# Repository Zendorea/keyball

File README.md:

# Keyball61 Wireless (PMW3610 / nice!nano / ZMK)

A fork of [Yowkees/keyball](https://github.com/Yowkees/keyball) for converting a
**Keyball61** (holykeebs Keyball61 rev2) to a **fully wireless** build:
**nice!nano v2 + ZMK**, with the power-hungry PMW3360 trackball sensor replaced by
the low-power **PMW3610**.

This fork holds the **hardware** side of that conversion — the custom PMW3610
sensor daughterboard. The **firmware** (ZMK) lives in a separate repo.

## What's here

- **[`keyball61_wireless/pmw3610_daughterboard/`](keyball61_wireless/pmw3610_daughterboard/)**
  — the PMW3610 trackball daughterboard: KiCad source, reproducible build
  pipeline, DRC-clean gerbers (ordered from PCBway), BOM, and full design notes.
  A drop-in replacement for the stock Keyball61 ball-reader board that keeps the
  original 7-pin connector and adds a MOTION interrupt line. **See its README.**
- **`keyball61/`** — the upstream Yowkees Keyball61 hardware design data (kept for
  reference: case, PCB, dimensions the daughterboard indexes to).

## Firmware (separate repo)

The wireless ZMK config is **`zmk-config-keyball61-wireless`** (standalone, as ZMK
configs must be). Trackball on `&spi1`: SCK P1.13, SDIO P0.10 (3-wire), CS P0.09,
MOTION P1.11, 2 MHz — based on the proven `tangbonze/zmk-config-Keyball61`.

## Project status

- ✅ Daughterboard: designed, DRC-clean, gerbers ordered (PCBway, ENIG, 1.0 mm)
- ✅ Parts sourced: PMW3610+LM18-LSI (AliExpress), passives/LDO (LCSC), 34 mm ball
- ✅ ZMK config: built (separate repo)
- ⬜ Assemble + flash when hardware arrives
- ⬜ (optional) main-board fork: nice!nano + nice!view

## Credits

Base keyboard design © [Yowkees / Keyball](https://github.com/Yowkees/keyball)
(see `LICENSE`). PMW3610 reference designs: siderakb / badjeff. Kit: holykeebs.

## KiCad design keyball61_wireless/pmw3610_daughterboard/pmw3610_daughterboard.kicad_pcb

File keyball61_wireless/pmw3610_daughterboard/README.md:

# PMW3610 Trackball Daughterboard — Keyball61 Wireless

Drop-in replacement for the stock Keyball61 PMW3360 ball-reader board, redesigned
for the low-power **PMW3610** sensor on a **nice!nano / ZMK** wireless build.
Keeps the stock Keyball **7-pin** connector at the exact original positions (drops
into a stock Keyball main board) and adds a **separate MOTION solder hole** so ZMK
can run the sensor interrupt-driven for best battery life.

**Status: final, DRC-clean, gerbers ordered from PCBway.**

## Board summary
- **23.0 × 25.0 mm**, 2-layer, **1.0 mm**, ENIG. U-shaped outline with a lens slot
  open to the top edge, sized to the **LM18-LSI** lens body.
- **PMW3610 optical center** at the original ball-facing position; connector +
  sensor share the X=11.0 mm centerline (ball centers on the IC via the stock
  Keyball cage).
- **7-pin connector** (CK·IO·G·V·G·CS·RST) at exact stock 2.54 mm positions +
  a separate **MOT** solder hole on the same pitch.
- Full PMW3610 support: **TLV74318** 1.8 V LDO + charge-pump/decoupling caps +
  NRESET & MOTION pull-ups. Solid B.Cu GND pour with stitching vias.
- DRC: **0 unrouted / 0 unconnected / 0 electrical / 0 hole-clearance**
  (5 non-fatal courtyard-overlap advisories — not fab-blocking).

## Files
| File | What it is |
|------|-----------|
| `DESIGN.md` | Full design spec: optics Z-stack, connector, MOTION, datasheet notes. |
| `BOM.csv` | As-built bill of materials with LCSC part numbers + cap-to-pin mapping. |
| `pmw3610_daughterboard.kicad_pcb` / `.kicad_pro` | Final routed board + project. |
| `pmw3610_daughterboard.kicad_dru` | Custom design rules (0.15 mm edge clearance). |
| `pmw3610_kb.pretty/` | The 3 custom footprints used: PMW3610 (siderakb), 7-pin connector, MOTION pad. |
| `fp-lib-table` | Resolves the local footprint lib on open. |
| `gerbers/` + `pmw3610_daughterboard_gerbers.zip` | Fab package (PCBway-ready): 7 gerbers + separate PTH/NPTH Excellon drills. |
| `drc.json` | Latest DRC report. |
| `board_final.png` / `board_top.png` / `board_bot.png` | Renders. |

## Reproducible build pipeline (KiCad 10 pcbnew + Freerouting 2.4.1)
Run in order (system `python3` with `pcbnew`, except footprints which use kiutils):
```
make_footprints_v2.py   -> custom footprints (sensor, 7-pin conn, MOTION pad)
build_board_22x25.py    -> place + net + design rules
export_dsn.py           -> Specctra DSN
Freerouting (headless, -mt 1, --router.via_costs=30, -inc GND)
import_ses.py           -> import routed session
pour_gnd.py             -> B.Cu GND pour (solid pad connection)
finish_22x25.py         -> GND stitching vias; fill zones last
kicad-cli pcb drc / export gerbers,drill
```

## Parts sourcing
- **Sensor + lens:** PMW3610DM-**SUDU** + **LM18-LSI** as a SET on AliExpress
  (not stocked at LCSC/Digikey). Match the lens (LM18-LSI) — avoid the 3360/LM19.
- **Passives + LDO + header:** LCSC (see `BOM.csv` for exact part numbers).
- **Ball:** 34 mm (Perixx PERIPRO-303 / SANWA).

## Firmware
Wireless ZMK config lives in a separate repo (`zmk-config-keyball61-wireless`):
trackball on `&spi1` — SCK P1.13, SDIO P0.10 (3-wire), CS P0.09, MOTION P1.11,
2 MHz. See that repo's README.

## Verify before assembly
- Sensor/lens standoff vs your trackball housing (base-plate sets focus, not PCB thickness).
- Continuity-check the sensor pins (esp. SCLK) after soldering — the most common DIY failure.

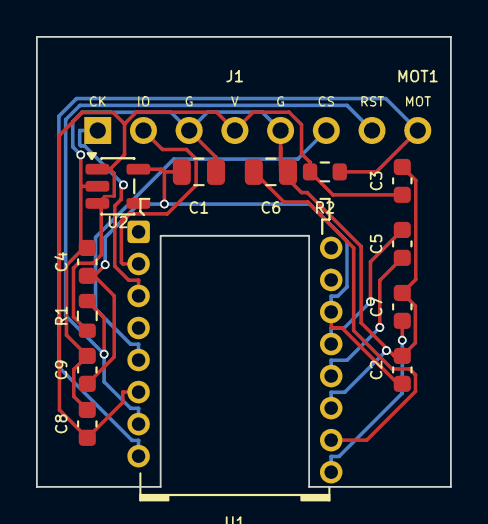
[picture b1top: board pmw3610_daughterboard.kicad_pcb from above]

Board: 2 copper layers, 23.0 x 25.0 mm, 15 parts (0 on the bottom side), 12 nets.

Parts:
C1: 3.3uF; C_0805_2012Metric
C2, C3, C4: 100nF; C_0603_1608Metric
C5, C7: 10nF; C_0603_1608Metric
C6: 10uF; C_0805_2012Metric
C8, C9: 1uF; C_0603_1608Metric
J1: Conn_Keyball_7pin; Conn_Keyball_7pin_stock
MOT1: MOTION; MOTION_solder_pad
R1, R2: 10k; R_0603_1608Metric
U1: PMW3610DM-SUDU; PMW3610DM-SUDU-siderakb
U2: TLV74318PDBVR; SOT-23-5

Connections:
+1V8: C1.1, C2.1, C4.1, C9.1, U1.14, U2.5
CN: C5.2, U1.13
CP: C5.1, U1.12
GND: C1.2, C2.2, C3.2, C4.2, C6.2, C7.2, C8.2, C9.2, J1.3, J1.5, U1.11, U2.2
MOTION: MOT1.1, R2.2, U1.8
NCS: J1.6, U1.5
NRESET: J1.7, R1.2, U1.7
PASST: C6.1, U1.10
SCLK: J1.1, U1.3
SDIO: J1.2, U1.2
VCC: C3.1, C8.1, J1.4, R1.1, R2.1, U1.6, U2.1, U2.3
VCP: C7.1, U1.9

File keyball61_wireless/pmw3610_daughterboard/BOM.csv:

Ref,Value,Footprint,LCSC,Qty,Notes
U1,PMW3610DM-SUDU,pmw3610_kb:PMW3610DM-SUDU,C42442560,1,Optical sensor; buy with LM18-LSI lens as a set
U2,TLV74318PDBVR,Package_TO_SOT_SMD:SOT-23-5,C485152,1,1.8V LDO
C1,3.3uF/16V,Capacitor_SMD:C_0805_2012Metric,C7393948,1,VDD bulk
C2,100nF,Capacitor_SMD:C_0603_1608Metric,C14663,1,VDD decouple
C3,100nF,Capacitor_SMD:C_0603_1608Metric,C14663,1,VDDIO decouple
C4,100nF,Capacitor_SMD:C_0603_1608Metric,C14663,1,sensor bulk (near pins)
C5,10nF,Capacitor_SMD:C_0603_1608Metric,C57112,1,charge pump CP-CN
C6,10uF,Capacitor_SMD:C_0805_2012Metric,C15850,1,PASS_T
C7,10nF,Capacitor_SMD:C_0603_1608Metric,C57112,1,VCP
C8,1uF,Capacitor_SMD:C_0603_1608Metric,C15849,1,LDO IN
C9,1uF,Capacitor_SMD:C_0603_1608Metric,C15849,1,LDO OUT
R1,10k,Resistor_SMD:R_0603_1608Metric,C25804,1,NRESET pull-up to +3V3
R2,10k,Resistor_SMD:R_0603_1608Metric,C25804,1,MOTION pull-up (DNP - use nice!nano internal pull-up)
J1,Conn_Keyball_8pin,pmw3610_kb:Conn_Keyball_8pin,,1,8-pin 2.54mm to main board; MOTION on pin 6
LENS,LM18-LSI,,,1,PixArt lens for PMW3610; buy bundled with U1
